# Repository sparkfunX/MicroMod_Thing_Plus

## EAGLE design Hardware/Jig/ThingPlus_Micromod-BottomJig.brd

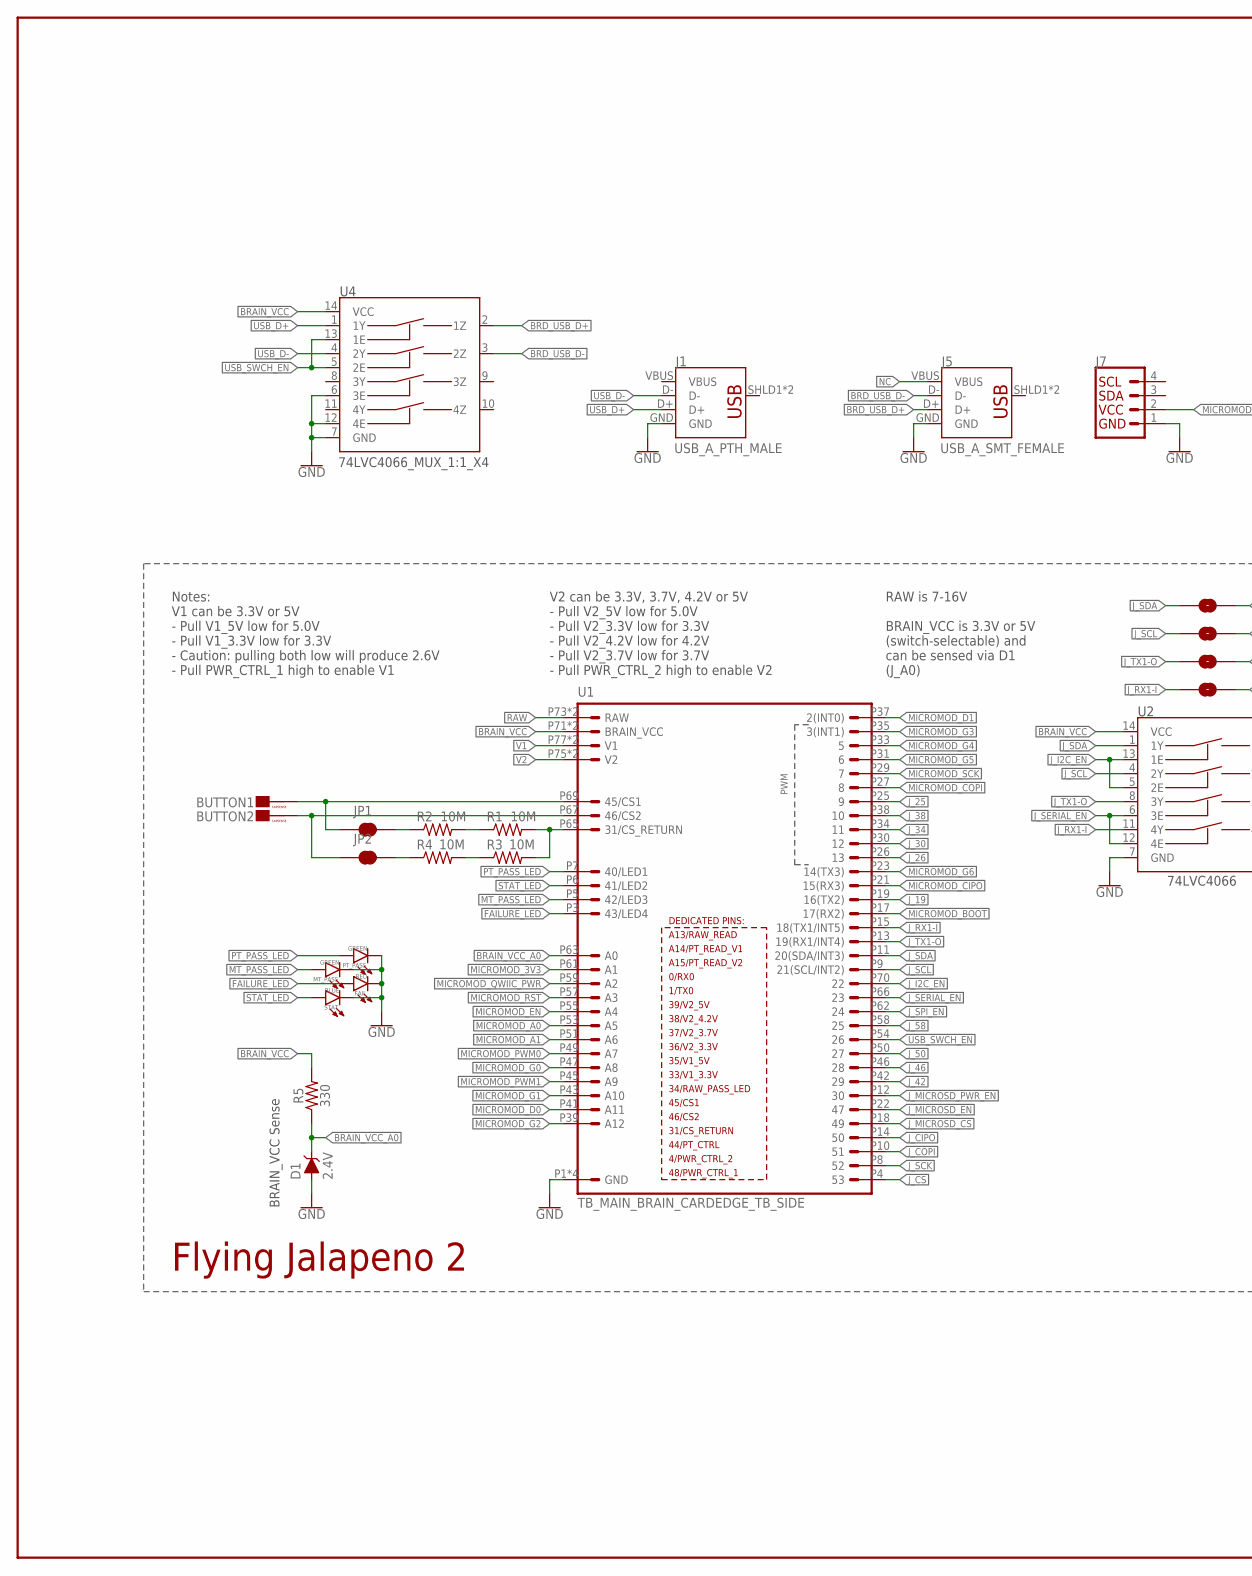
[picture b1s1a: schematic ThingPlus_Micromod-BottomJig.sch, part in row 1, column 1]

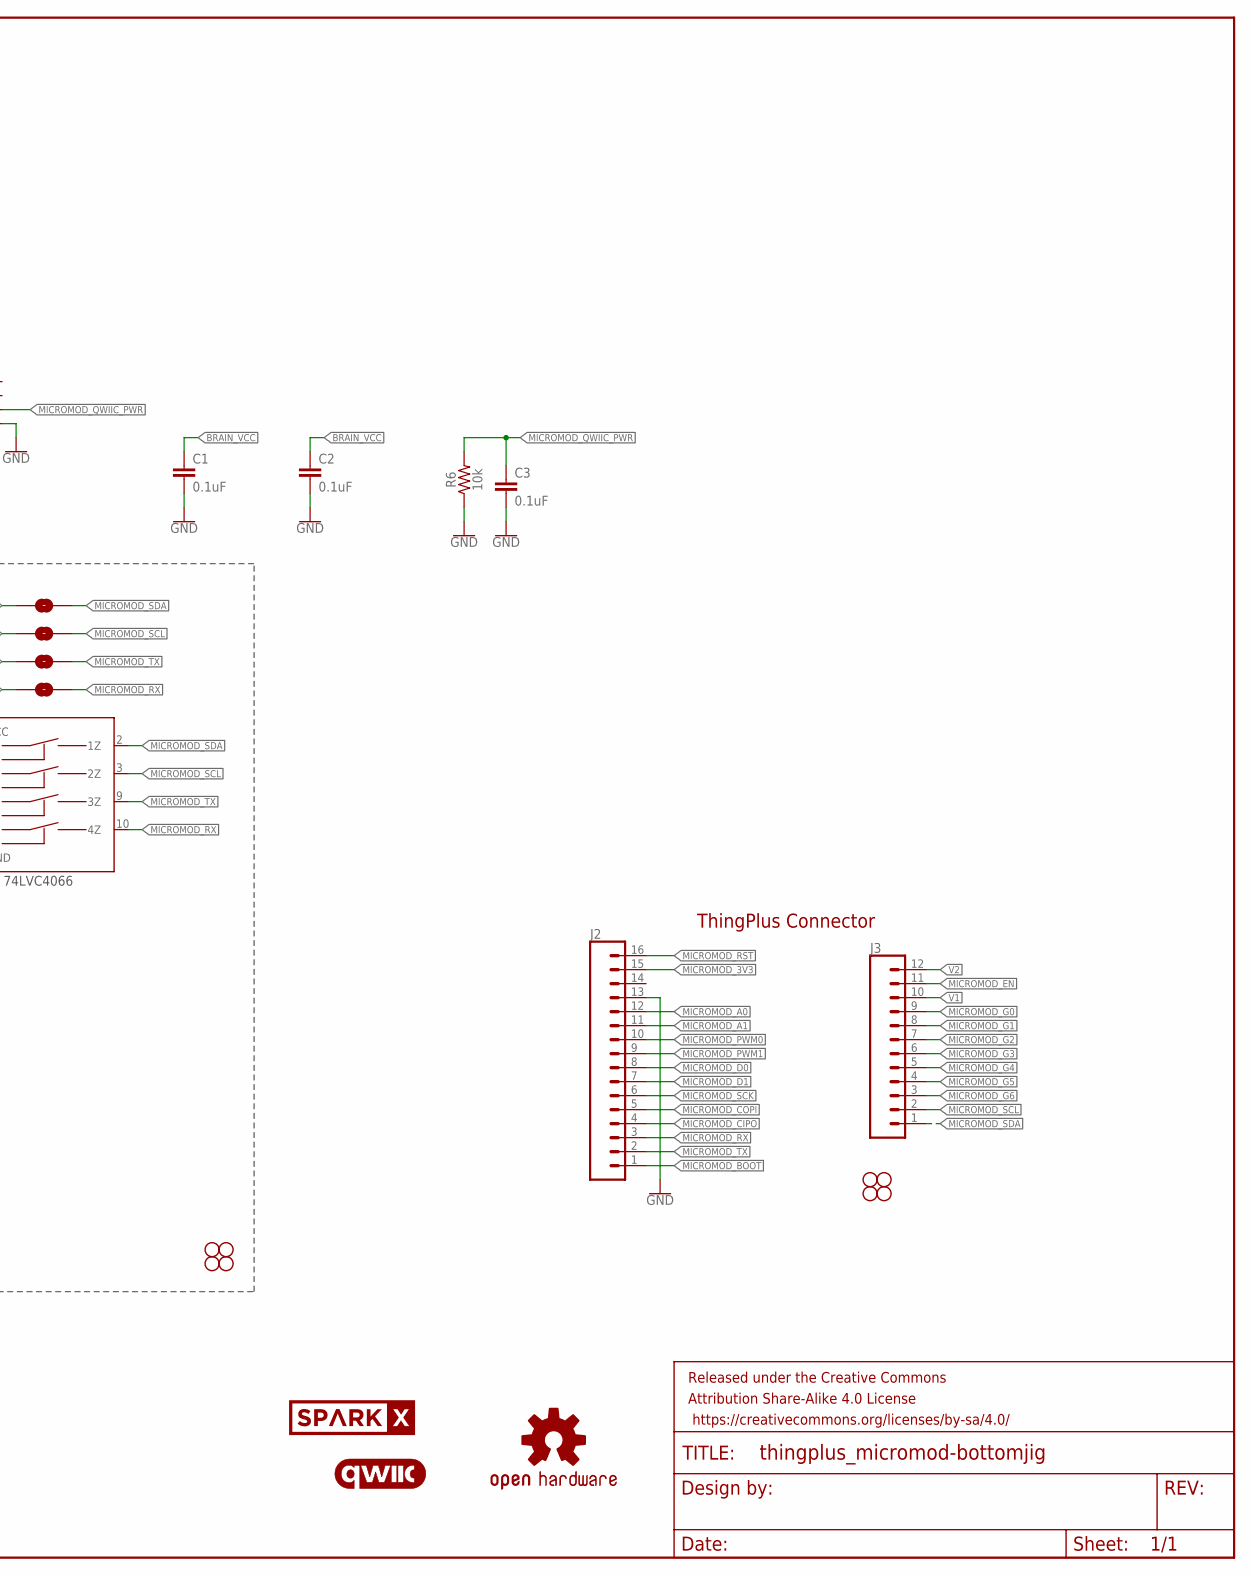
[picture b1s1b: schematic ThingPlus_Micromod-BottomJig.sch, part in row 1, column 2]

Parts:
BUTTON1, BUTTON2: CAPSENSE_BUTTON_PAD_ONLYV2_SMALL; CAPSENSE_BUTTON_PAD_ONLY_SM
C1, C2, C3: 0.1uF; 0603
D1: 2.4V; SOD-323
FAIL: RED; LED-1206
FRAME2: FRAME-LEDGER; CREATIVE_COMMONS
H1, H2, H3, H4, H5, H6, H7, H8: STAND-OFF
J1: USB_A_PTH_MALE; USB-A-H
J2: CONN_161X16_SM_SQ_NOSILK; 1X16_SM_SQ_NOSILK
J3: CONN_12SM_SQ_NO_SILK; 1X12_SM_SQ_NOSILK
J5: USB_A_SMT_FEMALE; USB-A-S-SILK-FEMALE
J7: QWIIC_RIGHT_ANGLE; JST04_1MM_RA
JP1, JP2: JUMPER-SMT_2_NC_TRACE_SILK; SMT-JUMPER_2_NC_TRACE_SILK
J_SCL, J_SCL1, J_SCL2: JUMPER-SMT_2_NO_SILK; SMT-JUMPER_2_NO_SILK
J_SDA: JUMPER-SMT_2_NO_SILK; SMT-JUMPER_2_NO_SILK
LOGO2: OSHW-LOGOMINI; OSHW-LOGO-MINI
LOGO4: QWIIC_LOGO_4MM; QWIIC_4MM
MT_PASS: GREEN; LED-1206
PT_PASS: GREEN; LED-1206
R1, R2, R3, R4: 10M; 0603
R5: 330; 0603
R6: 10k; 0603
STAT: BLUE; LED-1206
U1: TB_MAIN_BRAIN_CARDEDGE_TB_SIDE; TB_CARDEDGE
U2: 74LVC4066; SO14
U4: 74LVC4066_MUX_1:1_X4; SO14
U$1: SPARKX-LOGO4; SPARKX-MEDIUM

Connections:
!MICROMOD_BOOT!: J2.1, U1.P17 (17(RX2))
!MICROMOD_RST!: J2.16, U1.P57 (A3)
BRAIN_VCC: C1.1, C2.1, R5.2, U1.P71 (BRAIN_VCC), U1.P72 (BRAIN_VCC), U2.14 (VCC), U4.14 (VCC)
BRAIN_VCC_A0: D1.C, R5.1, U1.P63 (A0)
BRD_USB_D+: J5.D+, U4.2 (1Z)
BRD_USB_D-: J5.D-, U4.3 (2Z)
FAILURE_LED: FAIL.A, U1.P3 (43/LED4)
GND: C1.2, C2.2, C3.2, D1.A, FAIL.C, J1.GND, J2.13, J5.GND, J7.1, MT_PASS.C, PT_PASS.C, R6.1, STAT.C, U1.P1 (GND), U1.P2 (GND), U1.P79 (GND), U1.P80 (GND), U2.7 (GND), U4.6 (3E), U4.7 (GND), U4.12 (4E)
J_19: U1.P19 (16(TX2))
J_25: U1.P25 (9)
J_26: U1.P26 (13)
J_30: U1.P30 (12)
J_34: U1.P34 (11)
J_38: U1.P38 (10)
J_42: U1.P42 (29)
J_46: U1.P46 (28)
J_50: U1.P50 (27)
J_58: U1.P58 (25)
J_CIPO: U1.P14 (50)
J_COPI: U1.P10 (51)
J_CS: U1.P4 (53)
J_I2C_EN: U1.P70 (22), U2.5 (2E), U2.13 (1E)
J_MICROSD_!CS!: U1.P18 (49)
J_MICROSD_EN: U1.P22 (47)
J_MICROSD_PWR_EN: U1.P12 (30)
J_RX1-I: J_SDA.1, U1.P15 (18(TX1/INT5)), U2.11 (4Y)
J_SCK: U1.P8 (52)
J_SCL: J_SCL.1, U1.P9 (21(SCL/INT2)), U2.4 (2Y)
J_SDA: J_SCL2.1, U1.P11 (20(SDA/INT3)), U2.1 (1Y)
J_SERIAL_EN: U1.P66 (23), U2.6 (3E), U2.12 (4E)
J_SPI_EN: U1.P62 (24)
J_TX1-O: J_SCL1.1, U1.P13 (19(RX1/INT4)), U2.8 (3Y)
MICROMOD_3V3: J2.15, U1.P61 (A1)
MICROMOD_A0: J2.12, U1.P53 (A5)
MICROMOD_A1: J2.11, U1.P51 (A6)
MICROMOD_CIPO: J2.4, U1.P21 (15(RX3))
MICROMOD_COPI: J2.5, U1.P27 (8)
MICROMOD_D0: J2.8, U1.P41 (A11)
MICROMOD_D1: J2.7, U1.P37 (2(INT0))
MICROMOD_EN: J3.11, U1.P55 (A4)
MICROMOD_G0: J3.9, U1.P47 (A8)
MICROMOD_G1: J3.8, U1.P43 (A10)
MICROMOD_G2: J3.7, U1.P39 (A12)
MICROMOD_G3: J3.6, U1.P35 (3(INT1))
MICROMOD_G4: J3.5, U1.P33 (5)
MICROMOD_G5: J3.4, U1.P31 (6)
MICROMOD_G6: J3.3, U1.P23 (14(TX3))
MICROMOD_PWM0: J2.10, U1.P49 (A7)
MICROMOD_PWM1: J2.9, U1.P45 (A9)
MICROMOD_QWIIC_PWR: C3.1, J7.2, R6.2, U1.P59 (A2)
MICROMOD_RX: J2.3, J_SDA.2, U2.10 (4Z)
MICROMOD_SCK: J2.6, U1.P29 (7)
MICROMOD_SCL: J3.2, J_SCL.2, U2.3 (2Z)
MICROMOD_SDA: J3.1, J_SCL2.2, U2.2 (1Z)
MICROMOD_TX: J2.2, J_SCL1.2, U2.9 (3Z)
MT_PASS_LED: MT_PASS.A, U1.P5 (42/LED3)
unnamed: R1.2, R3.2, U1.P65 (31/CS_RETURN)
unnamed: R1.1, R2.2
unnamed: BUTTON1.CAPSENSE_PAD, JP1.1, U1.P69 (45/CS1)
unnamed: R3.1, R4.2
unnamed: JP2.2, R4.1
unnamed: BUTTON2.CAPSENSE_PAD, JP2.1, U1.P67 (46/CS2)
unnamed: JP1.2, R2.1
NC: J5.VBUS
PT_PASS_LED: PT_PASS.A, U1.P7 (40/LED1)
RAW: U1.P73 (RAW), U1.P74 (RAW)
STAT_LED: STAT.A, U1.P6 (41/LED2)
USB_D+: J1.D+, U4.1 (1Y)
USB_D-: J1.D-, U4.4 (2Y)
USB_SWCH_EN: U1.P54 (26), U4.5 (2E), U4.13 (1E)
V1: J3.10, U1.P77 (V1), U1.P78 (V1)
V2: J3.12, U1.P75 (V2), U1.P76 (V2)
VBUS: J1.VBUS

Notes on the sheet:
ThingPlus Connector
Flying Jalapeno 2
Notes: V1 can be 3.3V or 5V - Pull V1_5V low for 5.0V - Pull V1_3.3V low for 3.3V - Caution: pulling both low will produce 2.6V - Pull PWR_CTRL_1 high to enable V1
V2 can be 3.3V, 3.7V, 4.2V or 5V - Pull V2_5V low for 5.0V - Pull V2_3.3V low for 3.3V - Pull V2_4.2V low for 4.2V - Pull V2_3.7V low for 3.7V - Pull PWR_CTRL_2 high to enable V2
RAW is 7-16V BRAIN_VCC is 3.3V or 5V (switch-selectable) and can be sensed via D1 (J_A0)
BRAIN_VCC Sense

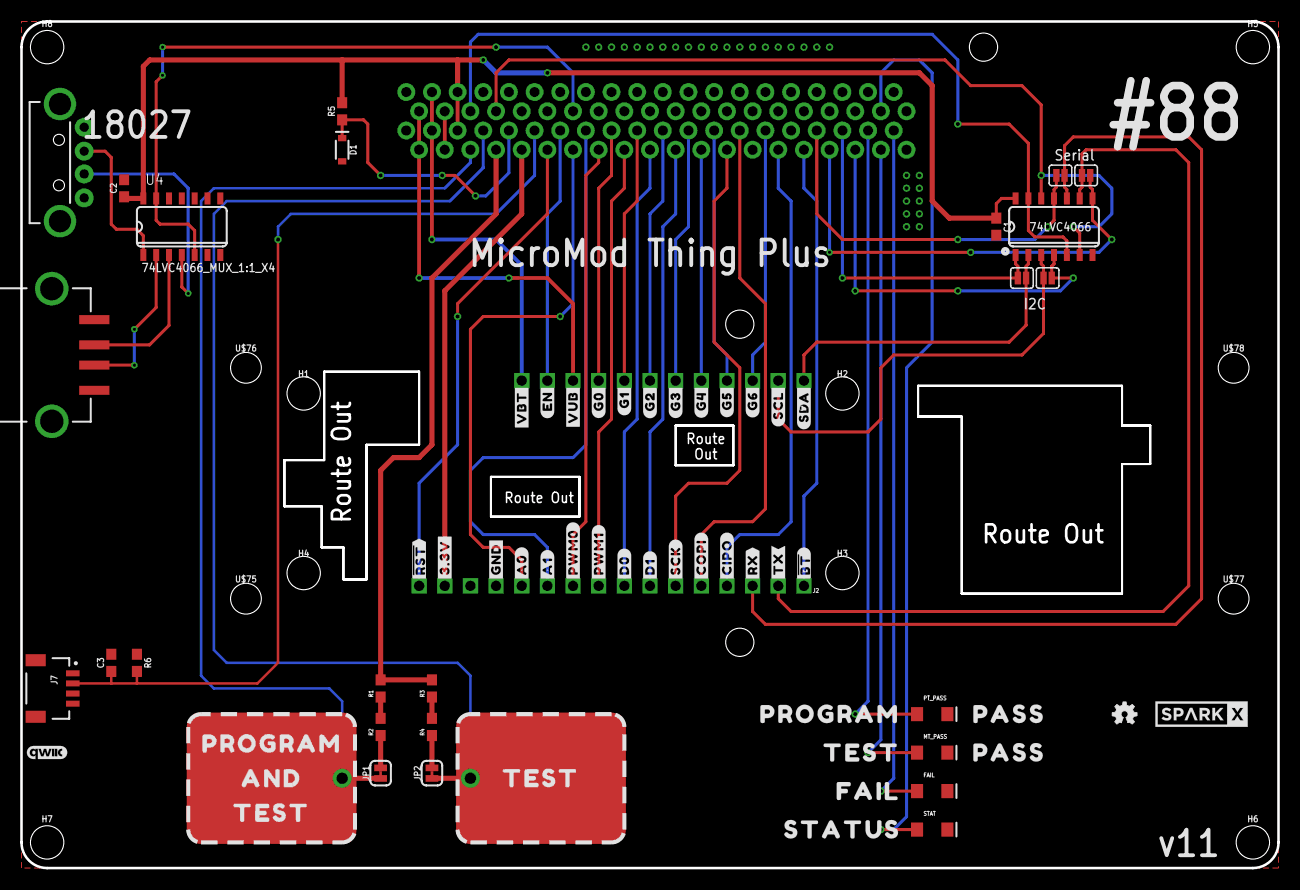
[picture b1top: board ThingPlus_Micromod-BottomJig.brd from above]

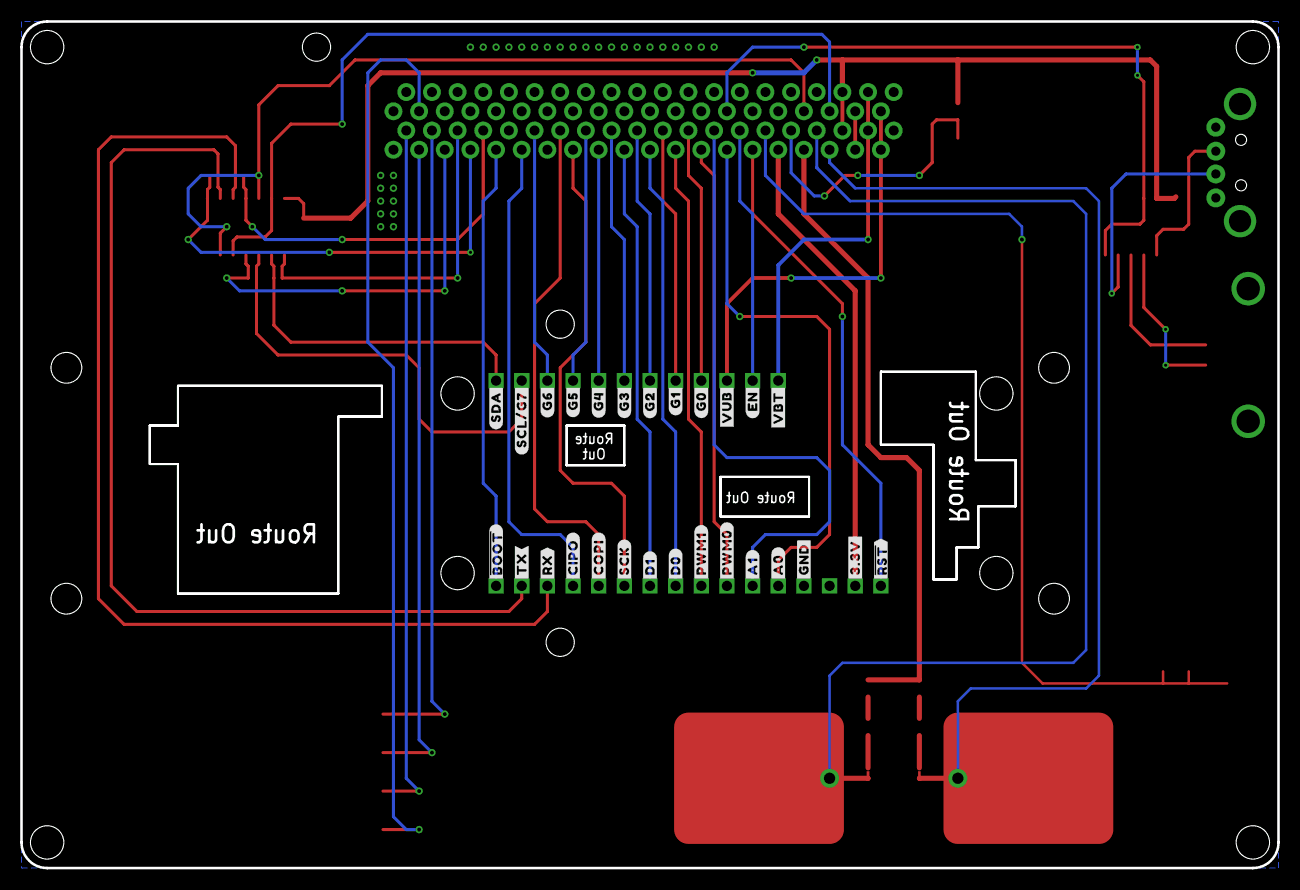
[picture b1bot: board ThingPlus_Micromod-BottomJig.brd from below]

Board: 2 copper layers, 124.5 x 83.8 mm, 112 parts (27 on the bottom side), 53 nets.

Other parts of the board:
U$3: ##BT##11
U$4, U$42: #TX#9
U$5, U$43: #RX#8
U$6, U$44: #CIPO#7
U$7, U$45: #COPI#6
U$8, U$46: #SCK#5
U$9, U$47: #D1#5
U$10, U$48: #D0#5
U$11, U$49: #PWM0#5
U$12, U$50: #PWM1#5
U$13, U$51: #A1#5
U$14, U$52: #A0#5
U$15, U$53: #GND#4
U$16, U$54: #3#3V#1
U$17, U$55: ##RST##0
U$22, U$57: #VBT#16
U$23, U$58: #EN#15
U$24, U$59: #G0#14
U$25, U$60: #G1#14
U$26, U$61: #G2#14
U$27, U$62: #G3#14
U$28, U$63: #G4#14
U$29, U$64: #G5#14
U$30, U$65: #G6#14
U$31: #SCL#13
U$32, U$67: #SDA#12
U$35, U$68: #VUB#15
U$56: ##BOOT##10
U$71: #SCL#G7#14
U$75, U$76, U$77, U$78: STAND-OFF-TIGHT
U$79, U$80: NUBBIN_LOCKER
U$82, U$83: PROGRAM0
U$84: AND0
U$85, U$86, U$87: TEST0
U$88, U$89: PASS0
U$90: FAIL0
U$91: STATUS0

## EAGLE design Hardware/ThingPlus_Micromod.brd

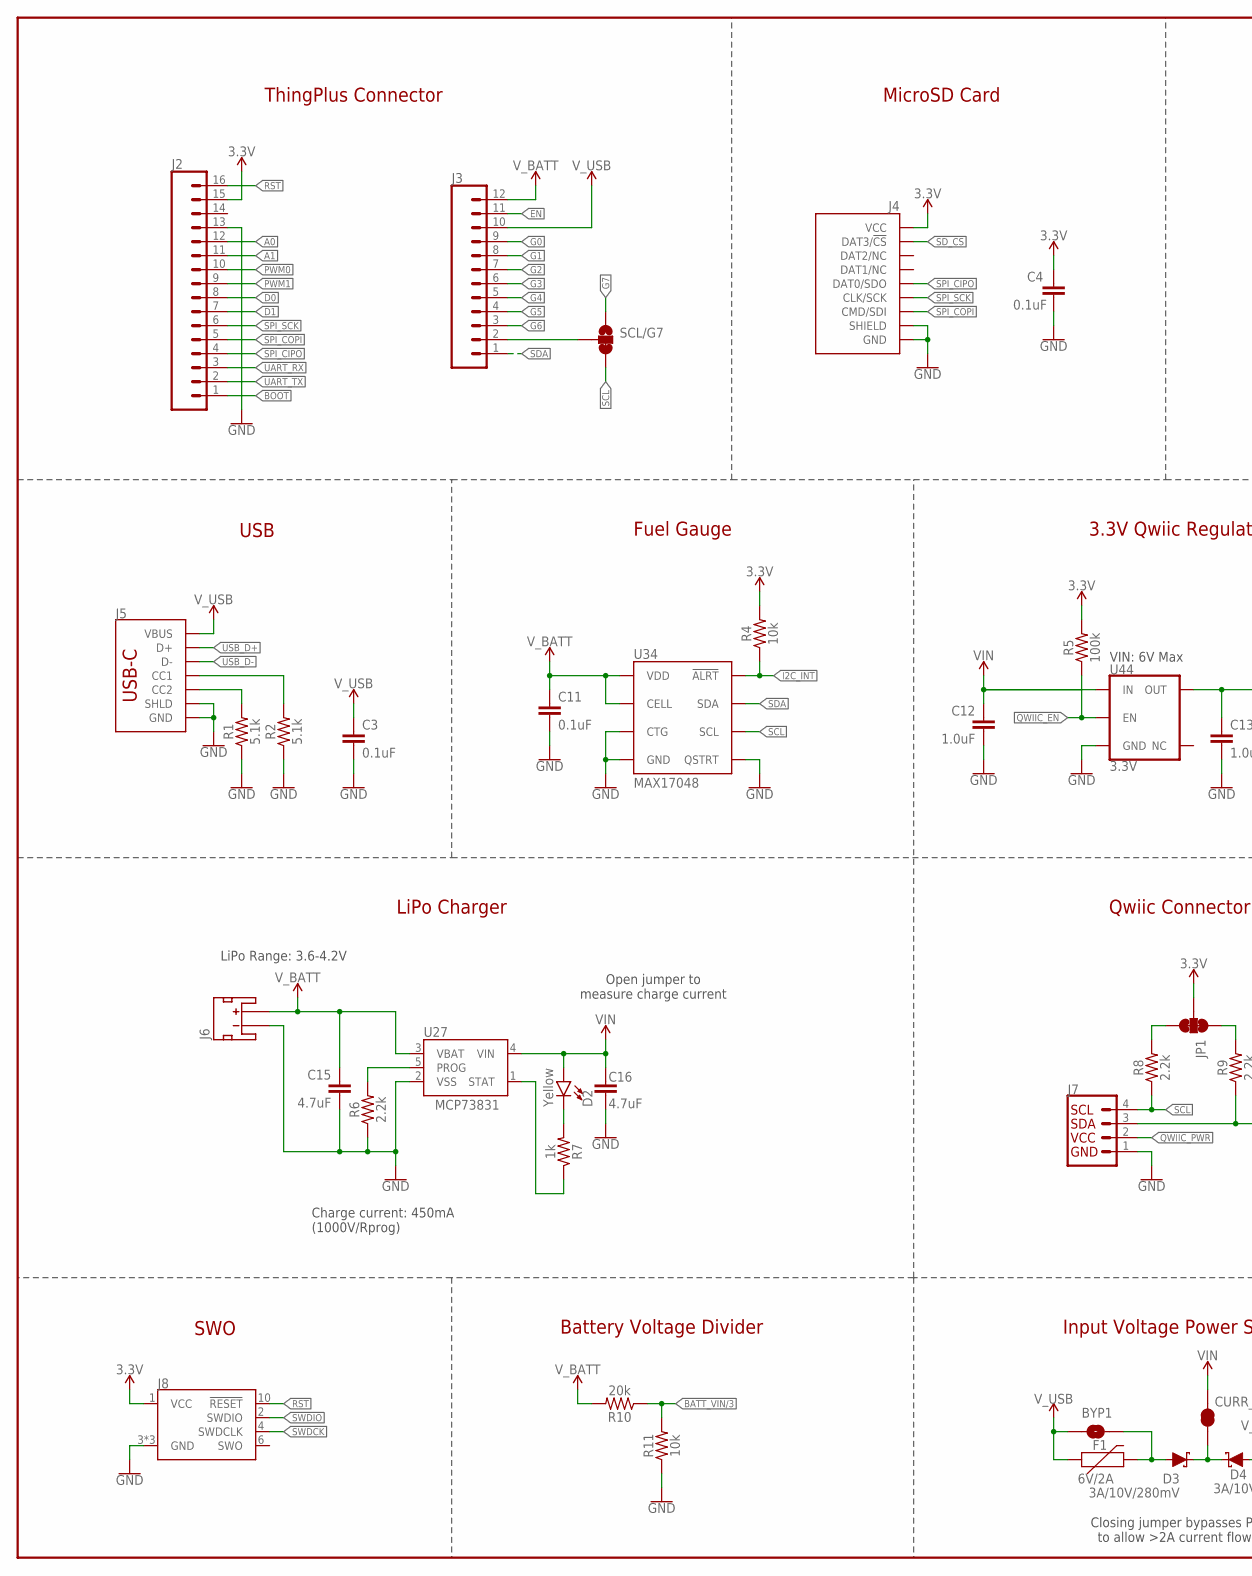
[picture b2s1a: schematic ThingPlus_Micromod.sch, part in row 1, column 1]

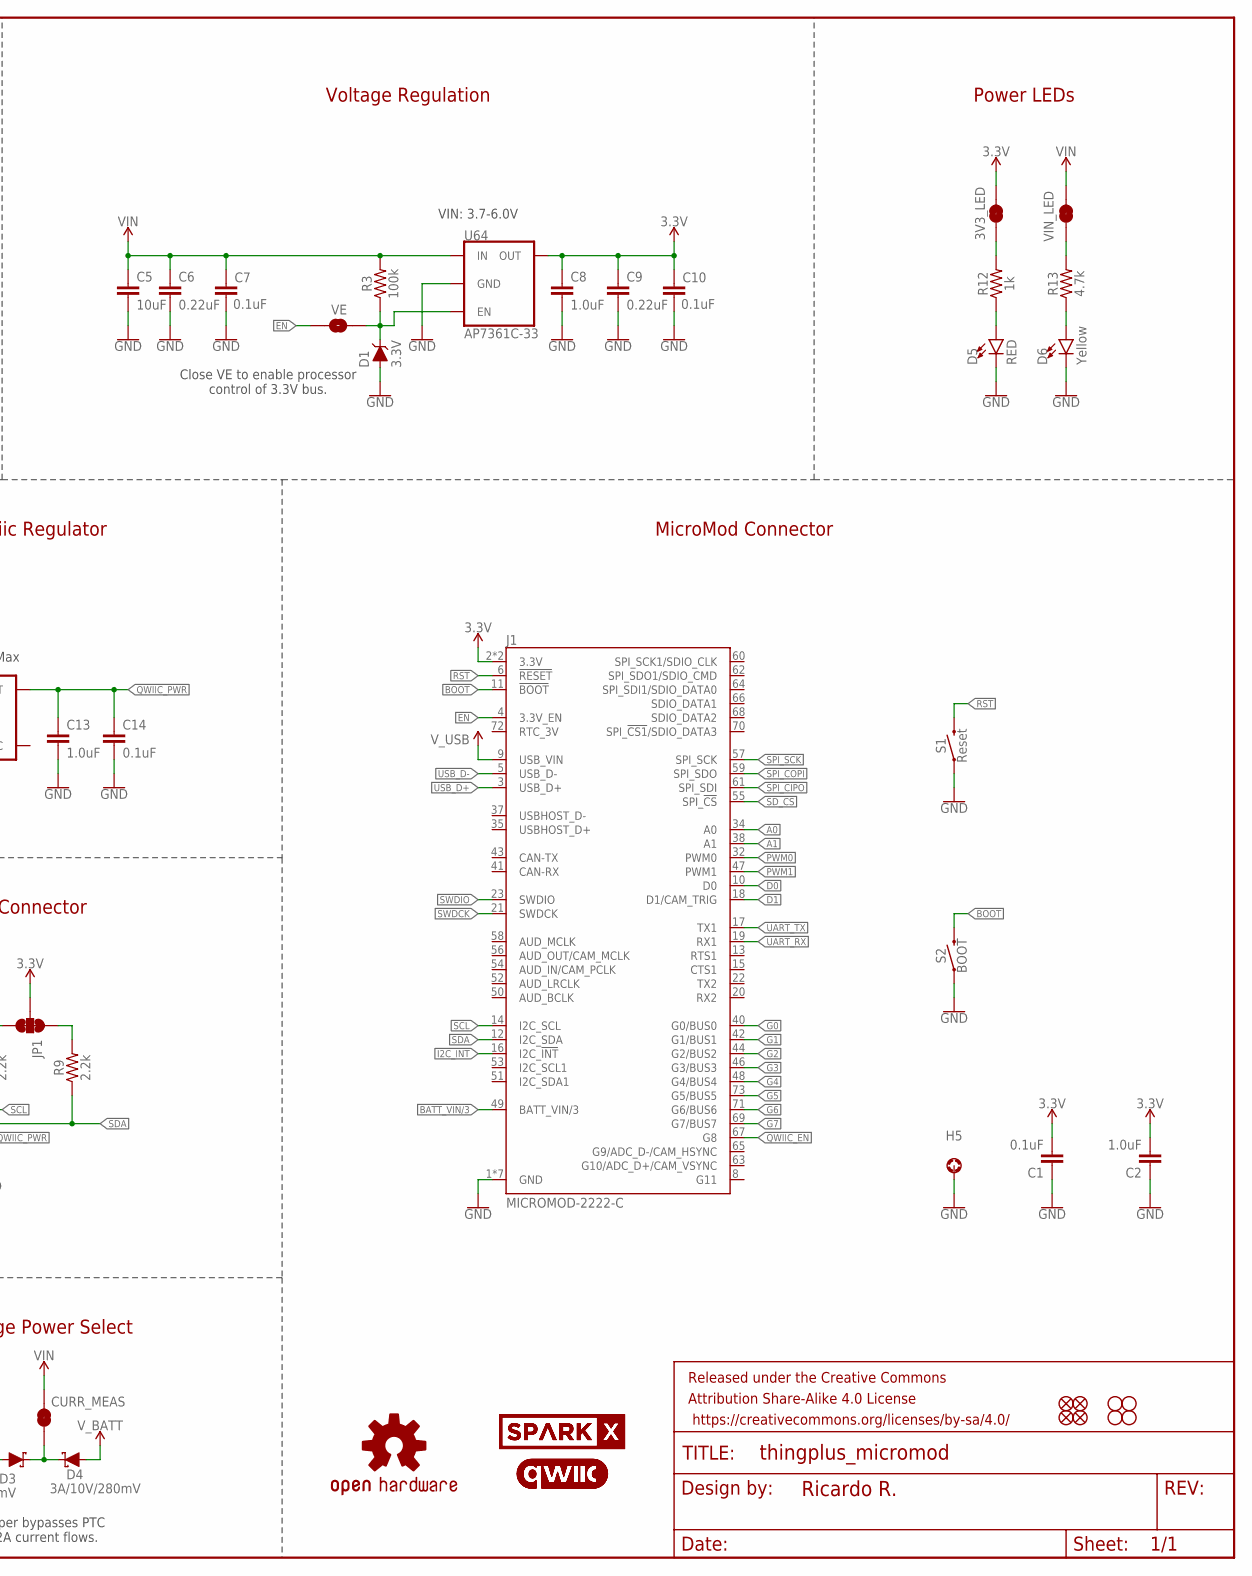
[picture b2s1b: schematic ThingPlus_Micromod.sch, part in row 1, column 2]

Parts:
3V3_LED: JUMPER-SMT_2_NC_TRACE_SILK; SMT-JUMPER_2_NC_TRACE_SILK
BYP1: JUMPER-SMT_2_NO_SILK; SMT-JUMPER_2_NO_SILK
C1, C3, C4, C7, C10, C11, C14: 0.1uF; 0603
C2, C8, C12, C13: 1.0uF; 0603
C5: 10uF; 0805
C6, C9: 0.22uF; 0603
C15, C16: 4.7uF; 0603
CURR_MEAS: JUMPER-COMBO_2_NC_TRACE; COMBO-JUMPER_2_NC_TRACE
D1: 3.3V; SOD-323
D2, D6: Yellow; LED-0603
D3, D4: 3A/10V/280mV; SOD-323
D5: RED; LED-0603
F1: 6V/2A; 1210
FD1, FD2, FD3, FD4: FIDUCIALUFIDUCIAL; FIDUCIAL-MICRO
FRAME1: FRAME-LEDGER; CREATIVE_COMMONS
H1, H2, H3, H4: STAND-OFF
H5: STAND-OFF-REFLOW2.5MM_TALL; STAND-OFF-REFLOW-M2.5
J1: MICROMOD-2222-C; M.2-CONNECTOR-E
J2: CONN_161X16_SM_SQ_NOSILK; 1X16_SM_SQ_NOSILK
J3: CONN_12SM_SQ_NO_SILK; 1X12_SM_SQ_NOSILK
J4: MICRO-SD-SDIOPUSH-PUSH; MICRO-SD-SOCKET
J5: USB_C_4-LAYER_PADS; USB-C-16P_4LAYER-PADS
J6: JST_2MM_MALE; JST-2-SMD
J7: QWIIC_RIGHT_ANGLE; JST04_1MM_RA
J8: JTAG; 2X5-PTH-1.27MM
JP1: JUMPER-SMT_3_2-NC_TRACE_SILK; SMT-JUMPER_3_2-NC_TRACE_SILK
LOGO1: OSHW-LOGOMINI; OSHW-LOGO-MINI
LOGO2, LOGO3: QWIIC_LOGO_4MM; QWIIC_4MM
R1, R2: 5.1k; 0603
R3, R5: 100k; 0603
R4, R11: 10k; 0603
R6, R8, R9: 2.2k; 0603
R7, R12: 1k; 0603
R10: 20k; 0603
R13: 4.7k; 0603
S1: Reset; TACTILE_SWITCH_SMD_5.2MM
S2: BOOT; TACTILE_SWITCH_SMD_5.2MM
SCL/G7: JUMPER-SMT_3_1-NC_TRACE_SILK; SMT-JUMPER_3_1-NC_TRACE_SILK
U27: MCP73831; SOT23-5
U34: MAX17048; DFN-8
U44: 3.3V; SOT23-5
U64: AP7361C-33; UDFN-8
U$1, U$2: SPARKX-LOGO5; SPARKX-LARGE
VE: JUMPER-SMT_2_NO_SILK; SMT-JUMPER_2_NO_SILK
VIN_LED: JUMPER-SMT_2_NC_TRACE_SILK; SMT-JUMPER_2_NC_TRACE_SILK

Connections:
3.3V: 3V3_LED.2, C1.2, C2.2, C4.1, C8.1, C9.1, C10.1, J1.2 (3.3V), J1.74 (3.3V), J2.15, J4.VCC, J8.1 (VCC), JP1.2, R4.2, R5.2, U64.1 (OUT)
3.3V_EN_VE: D1.C, R3.1, U64.5 (EN), VE.2
!BOOT!: J1.11 (!BOOT!), J2.1, S2.3 (2), S2.4 (2)
!I2C_INT!: J1.16 (I2C_!INT!), R4.1, U34.5 (!ALRT)
!RST!: J1.6 (!RESET!), J2.16, J8.10 (!RESET), S1.3 (2), S1.4 (2)
!SD_CS!: J1.55 (SPI_!CS!), J4.CS/DAT3 (DAT3/!CS!)
A0: J1.34 (A0), J2.12
A1: J1.38 (A1), J2.11
BATT_VIN/3: J1.49 (BATT_VIN/3), R10.1, R11.2
CHG_LED: R7.1, U27.1 (STAT)
D0: J1.10 (D0), J2.8
D1: J1.18 (D1/CAM_TRIG), J2.7
EN: J1.4 (3.3V_EN), J3.11, VE.1
G0: J1.40 (G0/BUS0), J3.9
G1: J1.42 (G1/BUS1), J3.8
G2: J1.44 (G2/BUS2), J3.7
G3: J1.46 (G3/BUS3), J3.6
G4: J1.48 (G4/BUS4), J3.5
G5: J1.73 (G5/BUS5), J3.4
G6: J1.71 (G6/BUS6), J3.3
G7: J1.69 (G7/BUS7), SCL/G7.1
GND: C1.1, C2.1, C3.2, C4.2, C5.2, C6.2, C7.2, C8.2, C9.2, C10.2, C11.2, C12.2, C13.2, C14.2, C15.2, C16.2, D1.A, D5.C, D6.C, H5.1, J1.1 (GND), J1.7 (GND), J1.33 (GND), J1.36 (GND), J1.39 (GND), J1.45 (GND), J1.75 (GND), J2.13, J4.CD1 (SHIELD), J4.GND, J4.GND1 (GND), J4.GND3 (GND), J5.GND, J5.GND2 (GND), J5.SHLD1 (SHLD), J5.SHLD2 (SHLD), J5.SHLD3 (SHLD), J5.SHLD4 (SHLD), J6.1 (-), J7.1, J8.3 (GND), J8.5 (GND), J8.9 (GND), R1.1, R2.1, R6.1, R11.1, S1.1, S1.2 (1), S2.1, S2.2 (1), U27.2 (VSS), U34.1 (CTG), U34.4 (GND), U34.6 (QSTRT), U34.9 (GND), U44.2 (GND), U64.4 (GND), U64.EP (GND)
unnamed: JP1.3, R8.2
unnamed: JP1.1, R9.2
unnamed: BYP1.2, D3.A, F1.2
unnamed: CURR_MEAS.1, CURR_MEAS.3 (1), D3.C, D4.C
unnamed: 3V3_LED.1, R12.2
unnamed: R6.2, U27.5 (PROG)
unnamed: D5.A, R12.1
unnamed: R13.2, VIN_LED.1
unnamed: D6.A, R13.1
unnamed: J5.A5 (CC1), R2.2
unnamed: J5.B5 (CC2), R1.2
unnamed: D2.C, R7.2
PWM0: J1.32 (PWM0), J2.10
PWM1: J1.47 (PWM1), J2.9
QWIIC_EN: J1.67 (G8), R5.1, U44.3 (EN)
QWIIC_PWR: C13.1, C14.1, J7.2, U44.5 (OUT)
SCL: J1.14 (I2C_SCL), J7.4, R8.1, SCL/G7.3, U34.7 (SCL)
SCL/G7: J3.2, SCL/G7.2
SDA: J1.12 (I2C_SDA), J3.1, J7.3, R9.1, U34.8 (SDA)
SPI_CIPO: J1.61 (SPI_SDI), J2.4, J4.DO/DAT0 (DAT0/SDO)
SPI_COPI: J1.59 (SPI_SDO), J2.5, J4.DI/CMD (CMD/SDI)
SPI_SCK: J1.57 (SPI_SCK), J2.6, J4.SCLK (CLK/SCK)
SWDCK: J1.21 (SWDCK), J8.4 (SWDCLK)
SWDIO: J1.23 (SWDIO), J8.2 (SWDIO)
UART_RX: J1.19 (RX1), J2.3
UART_TX: J1.17 (TX1), J2.2
USB_D+: J1.3 (USB_D+), J5.A6 (D+), J5.B6 (D+)
USB_D-: J1.5 (USB_D-), J5.A7 (D-), J5.B7 (D-)
VIN: C5.1, C6.1, C7.1, C12.1, C16.1, CURR_MEAS.2, CURR_MEAS.4 (2), D2.A, R3.2, U27.4 (VIN), U44.1 (IN), U64.8 (IN), VIN_LED.2
V_BATT: C11.1, C15.1, D4.A, J3.12, J6.2 (+), R10.2, U27.3 (VBAT), U34.2 (CELL), U34.3 (VDD)
V_USB: BYP1.1, C3.1, F1.1, J1.9 (USB_VIN), J3.10, J5.VBUS1 (VBUS), J5.VBUS2 (VBUS)

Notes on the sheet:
VIN: 6V Max
Fuel Gauge
3.3V Qwiic Regulator
Input Voltage Power Select
Qwiic Connector
Battery Voltage Divider
MicroSD Card
ThingPlus Connector
Voltage Regulation
Closing jumper bypasses PTC to allow >2A current flows.
VIN: 3.7-6.0V
Close VE to enable processor control of 3.3V bus.
USB
LiPo Charger
LiPo Range: 3.6-4.2V
Charge current: 450mA (1000V/Rprog)
Open jumper to measure charge current
SWO
MicroMod Connector
Power LEDs

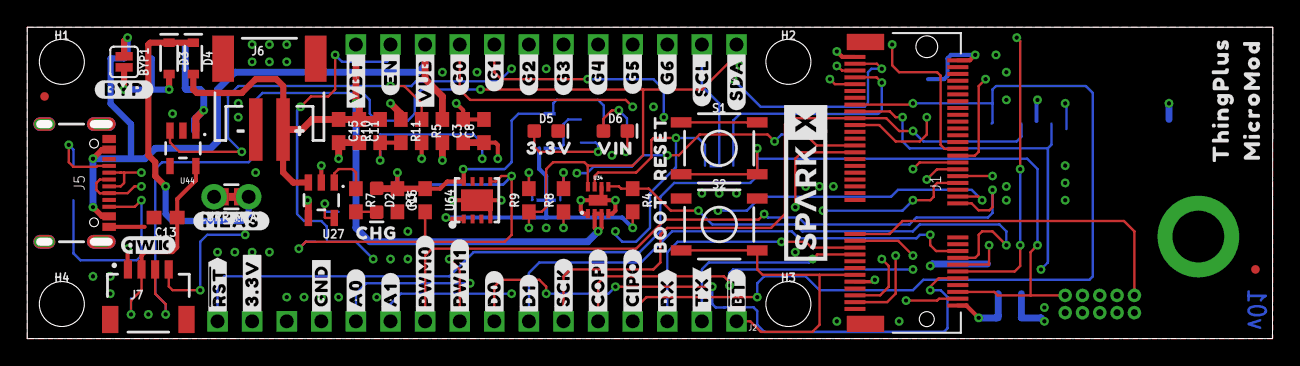
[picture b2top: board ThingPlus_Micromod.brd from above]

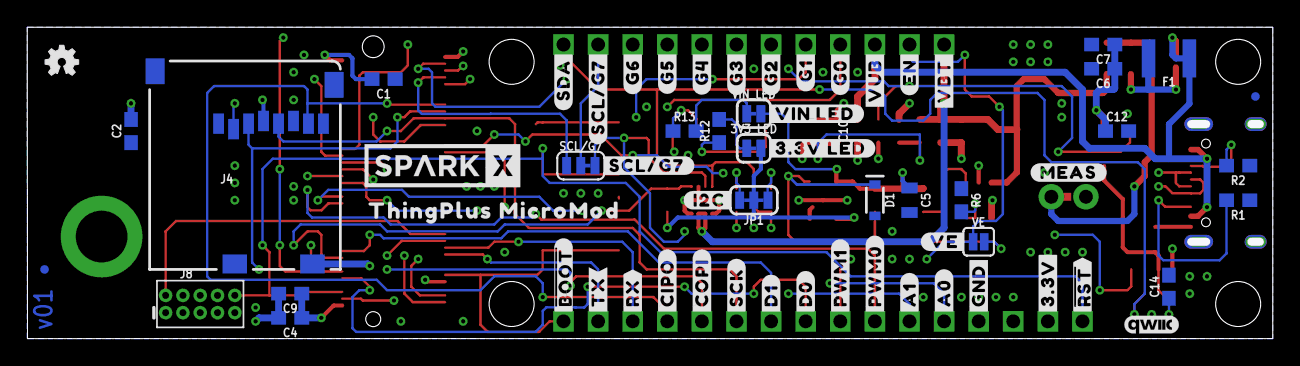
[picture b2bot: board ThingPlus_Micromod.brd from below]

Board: 4 copper layers, 91.4 x 22.9 mm, 144 parts (62 on the bottom side), 53 nets.

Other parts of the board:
U$3: ##BT##11
U$4, U$42: #TX#9
U$5, U$43: #RX#8
U$6, U$44: #CIPO#7
U$7, U$45: #COPI#6
U$8, U$46: #SCK#5
U$9, U$47: #D1#5
U$10, U$48: #D0#5
U$11, U$49: #PWM0#5
U$12, U$50: #PWM1#5
U$13, U$51: #A1#5
U$14, U$52: #A0#5
U$15, U$53: #GND#4
U$16, U$54: #3#3V#1
U$17, U$55: ##RST##0
U$18, U$66: #MEAS#25
U$19: CHG20
U$20: RESET19
U$21: BOOT18
U$22, U$57: #VBT#16
U$23, U$58: #EN#15
U$24, U$59: #G0#14
U$25, U$60: #G1#14
U$26, U$61: #G2#14
U$27, U$62: #G3#14
U$28, U$63: #G4#14
U$29, U$64: #G5#14
U$30, U$65: #G6#14
U$31: #SCL#13
U$32, U$67: #SDA#12
U$33: 3#3V22
U$34: VIN21
U$35, U$68: #VUB#15
U$36: THINGPLUS29
U$37: MICROMOD30
U$38: #31
U$39: #33
U$40: #BYP#27
U$41: #VE#16
U$56: ##BOOT##10
U$69: #3#3V_LED#25
U$70: #VIN_LED#25
U$71: #SCL#G7#14
U$72: #I2C#27
U$73: THINGPLUS_MICROMOD29
U$74: #SCL#G7#27

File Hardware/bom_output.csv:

Qty, PROD_ID, Names, Value, Package
7, CAP-00810, C1; C3; C4; C7; C10; C11; C14, 0.1uF, 0603
4, CAP-00868, C2; C8; C12; C13, 1.0uF, 0603
1, CAP-14259, C5, 10uF, 0805
2, CAP-07822, C6; C9, 0.22uF, 0603
1, CAP-08280, C15, 4.7uF, 0603
1, CAP-14106, C16, 4.7uF, 0603
1, DIO-11284, D1, 3.3V, SOD-323
2, DIO-09003, D2; D6, Yellow, LED-0603
2, DIO-14072, D3; D4, 3A/10V/280mV, SOD-323
1, DIO-00819, D5, RED, LED-0603
1, RES-14313, F1, 6V/2A, 1210
1, HW-14899, H5, STAND-OFF-REFLOW2.5MM_TALL, STAND-OFF-REFLOW-M2.5
1, CONN-14877, J1, MICROMOD-2222-C, M.2-CONNECTOR-E
1, CONN-07820, J4, MICRO-SD-SDIOPUSH-PUSH, MICRO-SD-SOCKET
1, CONN-14122, J5, , USB-C-16P_4LAYER-PADS
1, CONN-11443, J6, , JST-2-SMD
1, CONN-13694, J7, QWIIC_RIGHT_ANGLE, JST04_1MM_RA
2, RES-12083, R1; R2, 5.1k, 0603
2, RES-07828, R3; R5, 100k, 0603
2, RES-00824, R4; R11, 10k, 0603
3, RES-08272, R6; R8; R9, 2.2k, 0603
2, RES-07856, R7; R12, 1k, 0603
1, RES-09383, R10, 20k, 0603
1, RES-07857, R13, 4.7k, 0603
1, SWCH-14139, S1, Reset, TACTILE_SWITCH_SMD_5.2MM
1, SWCH-14139, S2, BOOT, TACTILE_SWITCH_SMD_5.2MM
1, IC-09995, U27, MCP73831, SOT23-5
1, IC-12551, U34, MAX17048, DFN-8
1, VREG-12457, U44, 3.3V, SOT23-5
1, VREG-14094, U64, AP7361C-33, UDFN-8

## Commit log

2021-01-21 Update SPI net names
2021-01-22 Corrected schematic, board layout WIP
2021-01-25 ThingPlus Micromod board routing WIP
2021-01-29 Preliminary version of routed board.
2021-01-29 Rename SCL/G7 net to SCL.
2021-01-30 Moved components to remove clearance errors; optimized GND and VCC polygons; fixed schematic off-grid components and fixed CamelCasing. TODO: add labels.
2021-02-03 Added buzzard labels to ThingPlus MicroMod
2021-02-03 Updated labeling placement.
2021-02-05 Updated layout per Nathan's recommendations
2021-02-05 Fixed off-grid wire in schematic
2021-02-11 Fixed wrong battery polarity in top silk; panelized design
2021-02-18 Fixed panel
2021-03-24 Added BOM
2021-05-24 Initial test jig layout - Work in progress
2021-05-25 Preliminary version of test jig bottom board uploaded
2021-05-30 Moved touch pad traces; added missing mounting hole; created top and middle jig boards;
2021-06-03 Added jig number, SKU and board names to test jig.
2021-06-04 Added milling polygons to bottom and middle jig boards; created Gerber files.
2021-06-04 Enlarged right board edge per JLCPCB request
2021-07-23 Updated board and middle jig
2021-07-26 Added TPMM test code
2021-07-26 Added SD card text file.
2021-07-26 Added conditional compilation for V10 board version.

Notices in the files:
parts and their libraries:
SparkFun-Jumpers: Licensing: Creative Commons ShareAlike 4.0 International - https://creativecommons.org/licenses/by-sa/4.0
SparkFun-Aesthetics: Released under the Creative Commons Attribution Share-Alike 4.0 License
SparkFun-Aesthetics: https://creativecommons.org/licenses/by-sa/4.0
